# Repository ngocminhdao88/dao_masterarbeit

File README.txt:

.
├── datasheet
├── design_of_experiment
│   └── articles
├── ehl_pruefstand
├── ladekurve_ebox
│   ├── img
│   ├── lib_fp.pretty
│   └── plot
├── latex
│   ├── aufgabenstellung
│   ├── chapters
│   ├── images
│   │   └── beschichtete_scheibe
│   ├── literatures
│   ├── tables
│   └── tips
├── lcr_ebox
│   ├── img
│   └── plot
├── literatures
│   ├── bader_Literatur
│   ├── dowson_elastohydrodynamic_lubrication
│   ├── ehl
│   ├── Elastohydrodynamic Lubrication
│   └── optical_capacitance_methods
├── messgeraete
│   ├── Ladekurven_Mobil
│   ├── ladekurven_programm
│   └── LCR-Meter ST2826
├── messungen
│   ├── auswertung_skipt
│   │   ├── kurve_bearbeiten
│   │   │   └── working
│   │   ├── lcr_meter
│   │   └── optische_messung
│   │       ├── __pycache__
│   │       └── working
│   ├── lcr_messung
│   ├── messungen_bei_vw
│   │   ├── 02052018VW
│   │   │   └── optisch
│   │   ├── 23052018VW
│   │   │   ├── DAQ card charging curves
│   │   │   ├── FVA3T40Load20N-26pF
│   │   │   ├── FVA3T40Load20N without 26pF
│   │   │   └── stmeter_plots
│   │   └── capacitance_analysed
│   │       ├── FVA_3
│   │       └── SHC_320
│   ├── oil_dielectric_constant
│   ├── rauheit
│   └── theory_film_thickness
├── presentations
│   └── bilde
├── rechnungen
└── schriftverkehr
    └── hai-chao_doe

57 directories

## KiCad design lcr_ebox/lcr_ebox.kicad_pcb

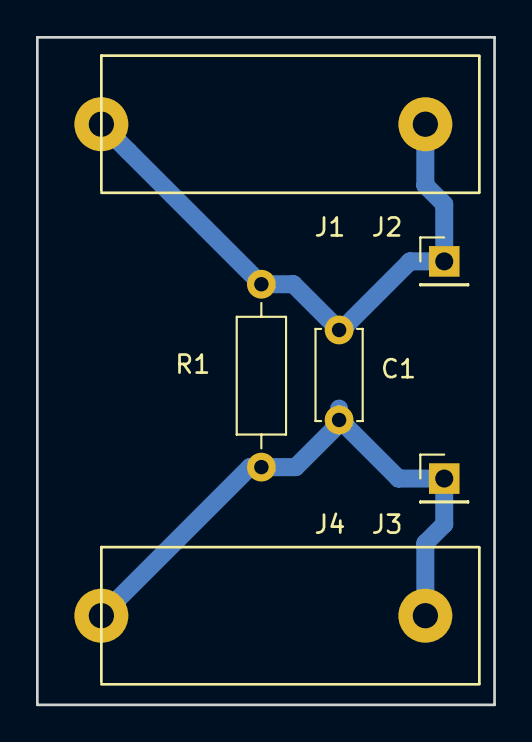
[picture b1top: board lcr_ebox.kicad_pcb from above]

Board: 2 copper layers, 25.4 x 37.1 mm, 6 parts (0 on the bottom side), 2 nets.

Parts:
C1: 22pF; C_Disc_D5.0mm_W2.5mm_P5.00mm
J1, J4: Conn_01x01_Female; Banana_Jack_1Pin_PCB
J2: A; PinHeader_1x01_P2.54mm_Vertical
J3: B; PinHeader_1x01_P2.54mm_Vertical
R1: 2k; R_Axial_DIN0207_L6.3mm_D2.5mm_P10.16mm_Horizontal

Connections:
unnamed: C1.1, J1.1, J2.1, R1.2
unnamed: C1.2, J3.1, J4.1, R1.1

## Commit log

2017-10-13 added ignore list for tex project and a Makefile
2017-10-16 Add preamble file. Ignore some files from preamble. Update Makefile
2017-10-18 Added some docs about the ehd rig of pcs instrument
2017-10-19 make some folder struktur change
2017-10-30 Added some literatures about optical and electrical methods
2017-11-01 Added IMKT powerpoint format. Sketleton of the presentation to VW. Rough layout of the thesis
2017-11-05 Updated the vw_presentation. Added some literatures
2017-11-05 Added the cover page
2017-11-06 Added nomenklatur, cheatsheets for latex symbols
2017-11-08 Added aufgabenstellung. Updated the presentation and the cover page
2017-11-15 Some change in the gliederung. Update the presentation for vw
2017-11-28 Changed the outline of the thesis
2017-11-30 Updated the bib
2017-11-30 Updated the make file and rename the file stand_der_technik
2017-11-30 Add some information to section: Eingenschaften des Schmierstoffes
2017-12-04 Added some ref. Working on chap 2
2017-12-11 Updated the presentation and continue to write the thesis
2017-12-18 Added some ref pics and diagrame. Wrote some for chapter 2
2018-01-11 update make file
2018-01-15 Worked on stand der technik. Changed the format to oneside
2018-01-16 Worked on 2.2 ehd-kontakt
2018-01-16 ehd kontakt
2018-01-17 Workded on ehd kontakt
2018-01-24 worked on kontakt von rauhen festkoerpern
2018-01-25 Added some pictures
2018-01-26 Update the image and bib
2018-01-27 Added newtonsche fluide
2018-01-27 added literatur
2018-02-02 working on stand der technik
2018-02-06 added Roelands literatur and fixed some spell check
2018-02-07 added some diagram
2018-02-08 worked on EHD-Schmierfilmdicke Dowson und Hamrock
2018-02-08 added literatur and finish the work on edh-filmthickness
2018-02-08 update the presentation
2018-02-11 added some literatur
2018-02-12 added cad file for glasscheibe_asm. Organised folder structure
2018-02-12 added gitignore file and the picture of default system
2018-02-13 Added assembly for kugel_support
2018-02-13 added a kaufliste and datasheets for cad
2018-02-15 finisched the ball and support assembly
2018-02-15 added some data sheets for glue and plastic
2018-02-15 Added a literatur about oil in sliding contact. Updated ehl cad
2018-02-15 added brush datasheet and update the cad.
2018-02-16 added datasheet about kohlenbuersten and update the cad
2018-02-16 updated the cad
2018-02-18 added datasheet for mack_kohlebuersten and kunstoffe_konstruieren
2018-02-18 added datashet for brush-holder mersen
2018-02-20 update drawing
2018-02-21 updated cad files and drawing
2018-02-21 added datasheet for kupferklebeband
2018-02-22 update the cad drawing and konstruktion
2018-02-22 Updated drawing
2018-02-23 Update the konstruktion and added the data sheet
2018-02-23 update construction
2018-02-24 Updated the konstruktion and added some datasheet for carbon brush and its holder
2018-02-26 Updated the konstrukton
2018-02-26 added arbeit von mach in literatur
2018-02-27 Updated the konstruktion. Release candidate
2018-02-27 Konstruktion: Added a parameter to add a part in BOM
2018-02-28 updated to the rc2 of konstruktion
2018-03-01 Konstruktion: Final version
2018-03-05 Added the invoices for the purcharsed components
2018-03-07 Added a section Reibung in Stand der Technik
2018-03-07 Fertig mit der Beschreibung der Reibung
2018-03-08 update the picture for reibung
2018-03-09 Working on chapter 4: PCS Prüfstand
2018-03-09 working on ehl test bench
2018-03-11 Done writing with Mechanischer Aufbau
2018-03-11 working on ehl messsystem
2018-03-12 modified the deckel (Buerstenhalter's position and pocket for the cable)
2018-03-12 done with messsystem. working on pruefstand aufbau
2018-03-13 done with documentation of ehl pruefstand
2018-03-14 working on elektrische Messmethoden
2018-03-15 Added some literatures and finished the widerstandmessung
2018-03-16 working on kapazitive messungen
2018-03-18 finished kapazitaetmessung
2018-03-19 finished the taktile messung
2018-03-20 added some literatures
2018-03-20 done with optische interferenz. Working on its variation
2018-03-21 finished variation of optical interference methode
2018-03-21 working on ultrashall
2018-03-22 finished schmierfilm mit ultrashall
2018-03-22 working on laser induced method
2018-03-23 fixed some images
2018-03-26 update the deckel. Bring den kohlenbuersten nach vorne
2018-03-26 added a section view for kugel asm
2018-03-26 working on konstruktive bearbeitung chapter
2018-03-27 working on writing konstruktion des Kugelsupports
2018-03-27 added a drawing of kohlebuerstenhalter_asm
2018-03-27 update the writing of konstruktion bearbeitung
2018-03-28 finished on writing of glasscheibebaugruppe
2018-03-28 update the drawing for documentation
2018-03-28 update the image for kugelsupport
2018-03-29 add some file of model to try rendering
2018-03-29 added obj file
2018-03-29 update image for kugelsupport
2018-04-04 finished writing about contructive works. Added some literatures
2018-04-04 add some drawing for documentation
2018-04-04 added a picture for the new cover and updated some pics. Working on capacitance messgeraet
2018-04-09 added some images of new coated spacer layer disc
2018-04-10 added some pictures and datasheets of messgereate
2018-04-10 done writing for ladekurven software
2018-04-10 added some article about the mess equipment and some picture
2018-04-11 change all the unit and number using siunitx package
2018-04-11 update some figures and done writing the lcr-meter
2018-04-16 Writen the einleitung. Update some picture and added kicad electronic box
2018-04-16 fixed some typo errors
2018-04-17 Added some equation and some literatur refs
2018-04-17 added some literatur quelle. Fixed the appendix
2018-04-17 added some lieteratures and a table of dynamic viscosity (ESDU)
2018-04-17 added some literatures. Added oil table from esdu and moved normen klatur to tables
2018-04-18 Updated some formular and update the normen klatur
2018-04-19 added all the pictures and some source for the used formulars
2018-04-19 added some literatures ansome contents to the appendix
2018-04-20 resolved the references conflict problem
2018-04-24 added guide lines for writing the Versuch and Zusammenfassung
2018-04-25 writing versuchdurchfurhrung
2018-05-06 added the messdaten
2018-05-07 continued to write on versuchsdurchfuehrung
2018-05-08 added the roughness measurement of the disc
2018-05-08 added some picture in versuchsausfuehrung. Added a measurement result
2018-05-08 added a table to show the settings for ladekurve gerate
2018-05-10 updated some picture
2018-05-11 added some picture and excel spreadsheet to calculate the theory film thickness
2018-05-12 added some pic and table to show how to measurement the roughness of the glasdisc
2018-05-13 add some picture and working on: how to measure the dielectric konstante of the oil
2018-05-14 working on writing how to measure the dielectric constant
2018-05-14 done writing how to measure the dielectric constante of th oil
2018-05-15 reorganized the working folder
2018-05-16 clean up the measurement datas and picture
2018-05-17 clean up the measurement files and done with the script to calculate the time constant of charging capacitor
2018-05-17 working script to fit and evaluate the capacitance
2018-05-19 added literatur from hai-chao
2018-05-22 working on design of experiment
2018-05-22 fix the script to calculate the theory film and capacitance of fva3 oil. Add a fig to show the influences of temp and load on the film_cap
2018-05-24 working on the script to analyse the measurement. Added a roughness measurement of the steel disc. Working on gramatic correction
2018-05-24 fixing gramatic errors
2018-05-25 first text's errors correction
2018-05-25 format the document. Added a dielectric constant for shc320. Added another script to calculate capacitance
2018-05-25 working curve fit using 2 points
2018-05-25 curve_fit_2points: press 'y' to save the data into a seperate file for later processing
2018-05-26 using class in curvefit_2points. Fix gramatic errors in text. Working on analyse data
2018-05-26 added a picture of the ebox and prepare optical meas datas
2018-05-27 added a picture of two disc and plot of verglech messungen
2018-05-27 added a final result
2018-05-28 done with writing the conclusion und result discusion
2018-05-28 fertig mit schreiben und bilde in chap 7 und 8
2018-05-28 added images of the whole system. Done with writing
2018-05-28 cut the assembly to rendering fotos
2018-06-01 working on the end presentation
2018-06-03 added some picture to the end presentation
2018-06-15 final presentation
